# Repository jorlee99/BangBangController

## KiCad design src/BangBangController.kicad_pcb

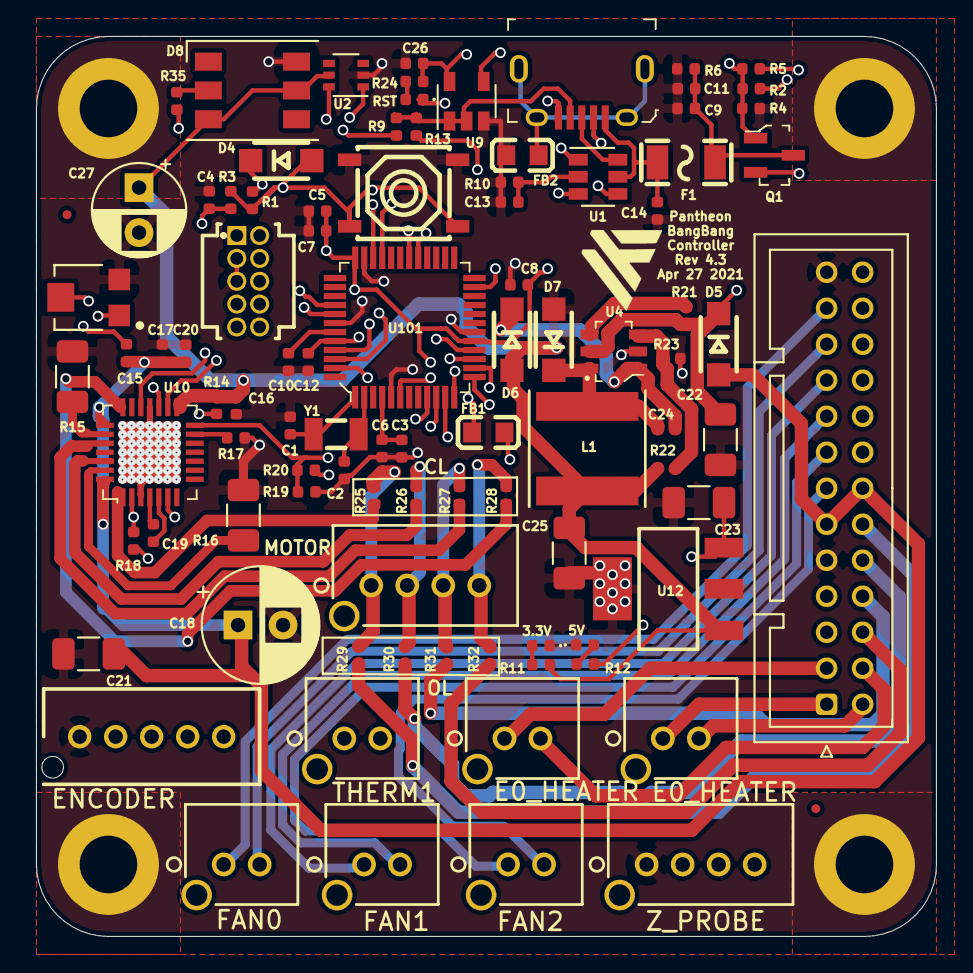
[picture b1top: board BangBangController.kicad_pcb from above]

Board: 4 copper layers, 50.0 x 50.0 mm, 99 parts (0 on the bottom side), 78 nets.

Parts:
C1, C2: 20pF; C_0402_1005Metric
C3: 4.7uF; C_0402_1005Metric
C4, C5, C6, C7, C12, C15, C16, C17, C20: 100nF; C_0402_1005Metric
C8: 10uF; C_0402_1005Metric
C9, C11, C26: 22uF; C_0402_1005Metric
C10: 1uF; C_0402_1005Metric
C13: 4.7nF; C_0402_1005Metric
C14, C24: 10nF; C_0402_1005Metric
C18: 47uF; CP_Radial_D6.3mm_P2.50mm
C19: 22nF; C_0402_1005Metric
C21: 1uF; C_1206_3216Metric
C22, C23: 47uF; C_1206_3216Metric
C25: 4.7uF; C_1206_3216Metric
C27: 470uF; CP_Radial_D5.0mm_P2.50mm
D1, D2, D3: LED; LED_0402_1005Metric
D4, D5, D6, D7: D_Zener; ss24fl
D8: WS2812; LED_WS2812_PLCC6_5.0x5.0mm_P1.6mm
F1: Fuse; fuse
FB1, FB2: Ferrite_Bead; L0603(FB)
FID1, FID2: Fiducial; Fiducial_0.5mm_Mask1mm
H1, H2, H3, H4: MountingHole; MountingHole_3.2mm_M3_DIN965_Pad
J1: Conn_02x13_Odd_Even; JST_PUD_B26B-PUDSS_2x13_P2.00mm_Vertical
J2: FTSH-105-01-F-D-K; SAMTEC_FTSH-105-01-F-D-K
J3: ENCODER; B05B-PASK-1
J5: FAN0; B02B-PASK-1LFSN
J6: FAN1; B02B-PASK-1LFSN
J8: FAN2; B02B-PASK-1LFSN
J9, J13: E0_HEATER; B02B-PASK-1LFSN
J10: THERM1; B02B-PASK-1LFSN
J11: Z_PROBE; B04B-PASK-1
J12: MOTOR; B04B-PASK-1
L1: 10uH; NR6028T100M
Q1: AO3401A; SOT-23-3
R1, R5, R6, R13, R23: 10K0; R_0402_1005Metric
R2: 270K0; R_0402_1005Metric
R3, R9: 330; R_0402_1005Metric
R4, R21, R22: 52K3; R_0402_1005Metric
R10: 1M0; R_0402_1005Metric
R11: 270R; R_0402_1005Metric
R12, R24: 150R; R_0402_1005Metric
R14: 20K; R_0402_1005Metric
R15, R16: 0R15; R_1206_3216Metric
R17, R18, R19: 20K0; R_0402_1005Metric
R20: 1K0; R_0402_1005Metric
R25, R26, R27, R28, R29, R30, R31, R32: R; R_0402_1005Metric
R35: 470; R_0402_1005Metric
RV1: 20K; TRIM_TC33X-2-203E
S1: RST; reset_button
U1: USBLC6-2SC6; SOT-23-6
U2: 74LVC2G17; SOT-363_SC-70-6
U4: AOZ1280CI; SOT-23-6
U8: USB_B_Micro; USB_Micro_B_Female_10118194-0001LF
U9: SN74LVC1G125DBVT; SOT-23-5
U10: TMC2208-LA-T; VFQFN-28-1EP_5x5mm
U12: TC1262-33; SOT-223_L6.5-W3.5-P2.30-LS7.0-BR
U101: ATSAMD21G18A-AUT; TQFP-48_7x7mm
Y1: 32.76KHz; FC-135R_L3.2-W1.5

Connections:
+3V3: C5.1, C7.1, C8.1, C12.1, C23.1, C26.2, D4.1, FB1.2, J2.01, J3.4, R1.1, R12.1, R13.1, R24.1, U9.5, U12.3, U101.17, U101.36, U101.44
+5V: C16.1, C25.1, C27.1, D6.2, D8.3, D8.5, J11.3, L1.2, Q1.2, R5.1, R11.1, R14.1, R18.2, R22.1, U2.5, U10.15, U12.1
+24V: C15.1, C17.1, C18.1, C20.1, C21.1, D5.2, J1.11, J1.14, U10.22, U10.28
/Sheet5F7F862D/RST: C4.2, R3.1, U101.40
/Sheet5F7F862D/SWCLK: J2.04, U101.45
/Sheet5F7F862D/SWDIO: J2.02, U101.46
A3: J3.3, U101.9
A4: J3.2, U101.10
A5: R18.1, U10.2, U101.47
AREF: C3.2, C6.2, U101.4
D0\RX: R19.1, R20.2, U10.14, U101.16
D1\TX: R20.1, U101.15
D2: U2.1, U101.23
D3: J1.18, U101.14
D4: J1.16, U101.13
D6: U10.19, U101.29
D7: U10.16, U101.30
D8: J3.1, U101.11
D9: J1.20, U101.12
DN: U1.3, U101.33
DP: U1.1, U101.34
E0+: J1.2, J1.4, J9.2, J13.2
E0-: J1.1, J1.3, J9.1, J13.1
E0_A1: J1.10, R30.2
E0_A2: J1.12, R29.2
E0_B1: J1.8, R31.2
E0_B2: J1.6, R32.2
GND: C1.1, C2.1, C3.1, C4.1, C5.2, C6.1, C7.2, C8.2, C9.2, C10.2, C11.2, C12.2, C13.1, C14.2, C16.2, C17.2, C18.2, C20.2, C21.2, C22.2, C23.2, C25.2, C26.1, C27.2, D1.1, D2.1, D7.2, D8.6, FB2.1, H1.1, H2.1, H3.1, H4.1, J1.9, J1.25, J2.03, J2.05, J3.5, J11.1, R4.2, R6.2, R10.1, R15.2, R16.2, R17.2, R19.2, R23.2, RV1.3, S1.1, S1.2, U2.2, U4.2, U8.5, U9.3, U10.3, U10.18, U10.29, U12.2, U101.5, U101.18, U101.35, U101.42
ID: R9.2, R13.2, U8.4, U9.1, U9.2
unnamed: C1.2, U101.1, Y1.1
unnamed: C2.2, U101.2, Y1.2
unnamed: C10.1, U101.43
unnamed: C9.1, C11.1, F1.2, Q1.3, R6.1
unnamed: C15.2, U10.6
unnamed: C19.1, U10.4
unnamed: C19.2, U10.5
unnamed: C24.1, D6.1, U4.1
unnamed: C24.2, D7.1, L1.1, U4.6
unnamed: D1.2, R11.2
unnamed: D2.2, R12.2
unnamed: D3.1, D4.2, J2.10, R1.2, R3.2, S1.3, S1.4
unnamed: D3.2, R24.2
unnamed: D8.2, R35.1
unnamed: FB1.1, U101.6
unnamed: FB2.2, U8.6
unnamed: J12.1, R25.1, R29.1
unnamed: J12.2, R26.1, R30.1
unnamed: J12.3, R27.1, R31.1
unnamed: J12.4, R28.1, R32.1
unnamed: Q1.1, R2.1, R4.1, R5.2, U9.4
unnamed: R14.2, RV1.1
unnamed: R15.1, U10.23
unnamed: R16.1, U10.27
unnamed: R17.1, U10.13
unnamed: R21.2, U4.4
unnamed: R22.2, R23.1, U4.3
unnamed: R25.2, U10.1
unnamed: R26.2, U10.26
unnamed: R27.2, U10.24
unnamed: R28.2, U10.21
unnamed: R35.2, U2.6
unnamed: U1.4, U8.2
unnamed: U1.6, U8.3
SH: C13.2, R10.2, U1.2
THERMISTOR1: J1.5, J10.2
USB_EN: R9.1, U101.41
VBUS: C14.1, F1.1, U1.5, U8.1
VIN_SW: C22.1, D5.1, R2.2, R21.1, U4.5
VREF: RV1.2, U10.17
VSSA: J1.7, J10.1
V_FAN0+: J1.21, J5.2
V_FAN0-: J1.23, J5.1
V_FAN1+: J1.17, J6.2
V_FAN1-: J1.19, J6.1
V_FAN2+: J1.13, J8.2
V_FAN2-: J1.15, J8.1
Z_PROBE_IN: J1.22, J11.4
Z_PROBE_MOD: J1.26, J11.2

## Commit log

2021-06-02 Test change

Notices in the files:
parts and their libraries:
Copyright 2016 Accelerated Designs. All rights reserved.
